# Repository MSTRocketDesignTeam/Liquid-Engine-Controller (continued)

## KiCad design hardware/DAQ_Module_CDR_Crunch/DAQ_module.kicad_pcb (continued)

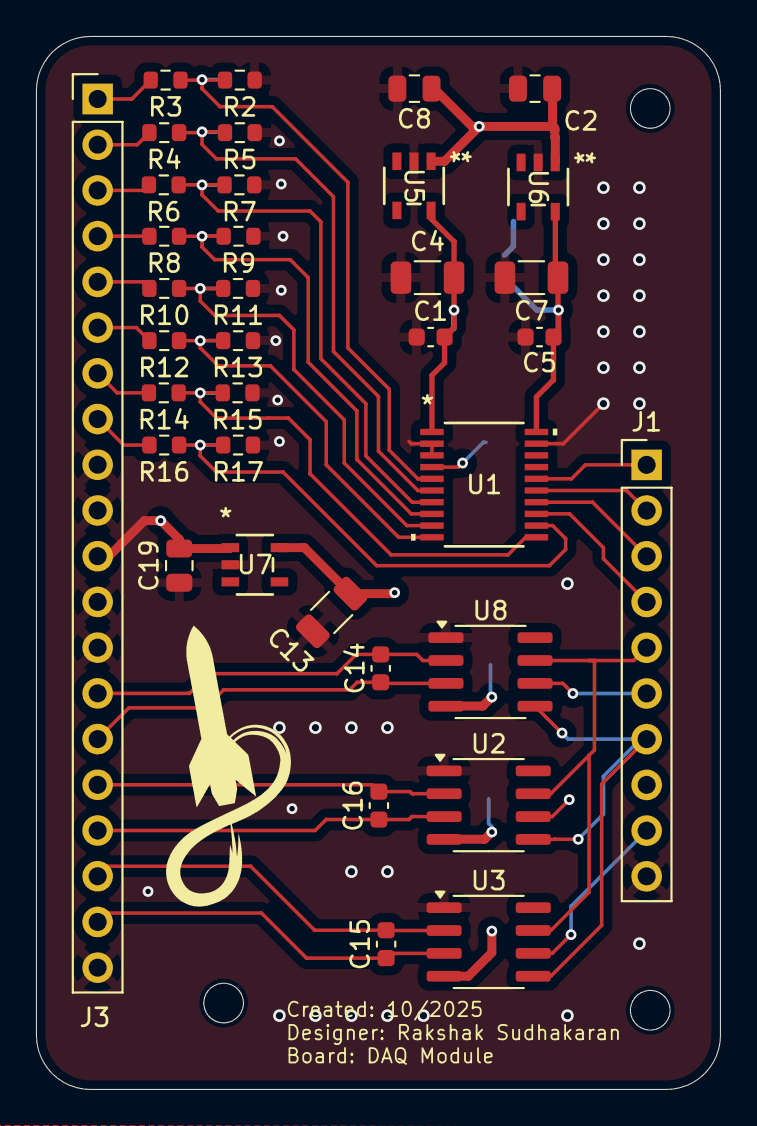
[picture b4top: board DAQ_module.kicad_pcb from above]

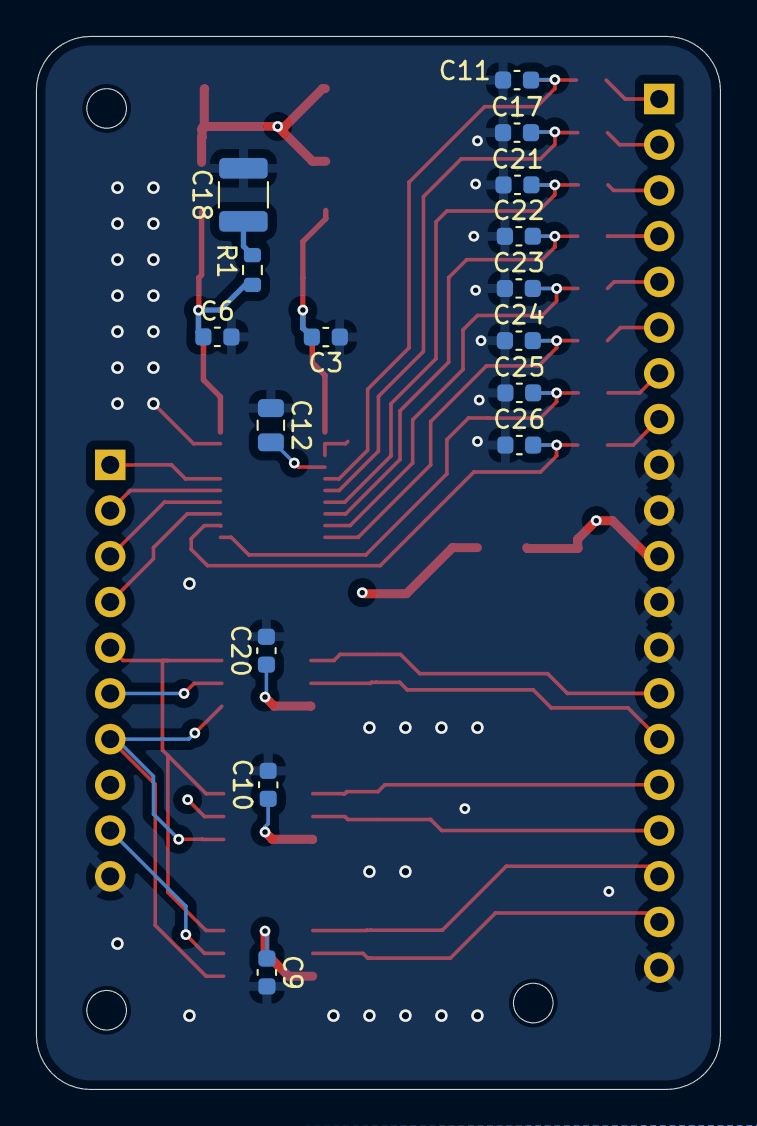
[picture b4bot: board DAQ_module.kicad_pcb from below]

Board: 4 copper layers, 38.0 x 58.5 mm, 52 parts (16 on the bottom side), 38 nets.

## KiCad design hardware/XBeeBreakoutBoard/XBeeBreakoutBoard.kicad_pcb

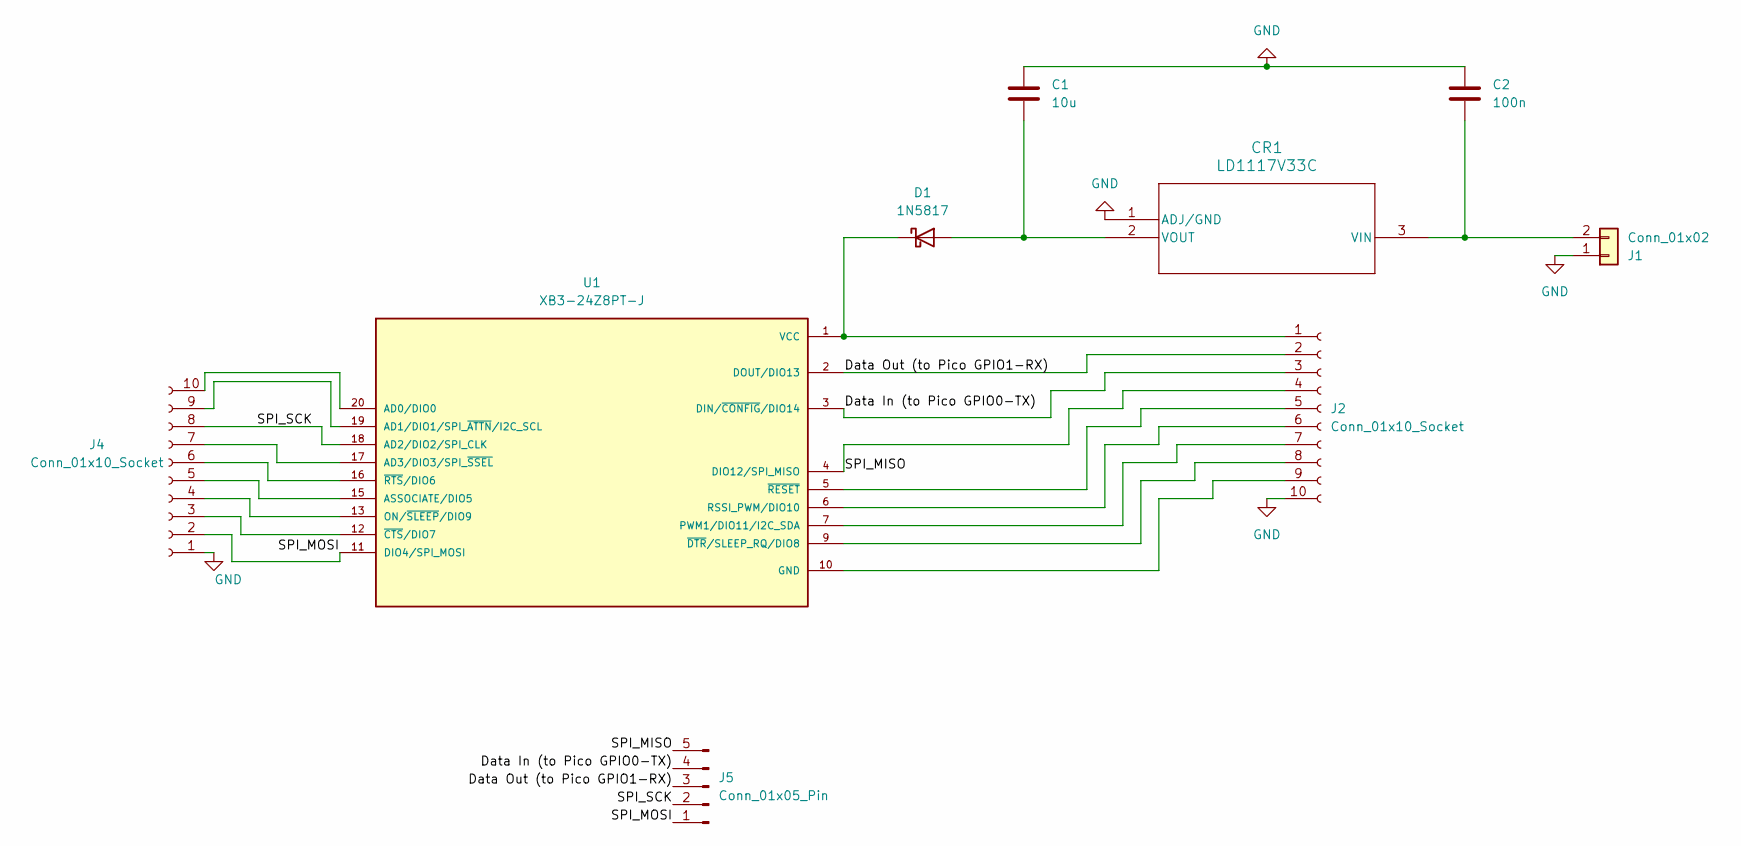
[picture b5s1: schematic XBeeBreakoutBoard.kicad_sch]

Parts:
C1: 10u; C_0805_2012Metric
C2: 100n; C_0603_1608Metric
CR1: LD1117V33C; TO-220_STM
D1: 1N5817; D_DO-41_SOD81_P10.16mm_Horizontal
J1: Conn_01x02; AMASS_XT30UPB-M_1x02_P5.0mm_Vertical
J2, J4: Conn_01x10_Socket; PinSocket_1x10_P2.54mm_Vertical
J5: Conn_01x05_Pin; PinSocket_1x05_P2.54mm_Vertical
U1: XB3-24Z8PT-J; XCVR_XB3-24Z8PT-J; PARTREV N/A

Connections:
/Data In (to Pico GPIO0-TX): J2.3, J5.4, U1.3 (DIN/~CONFIG/DIO14)
/Data Out (to Pico GPIO1-RX): J2.2, J5.3, U1.2 (DOUT/DIO13)
/SPI_MISO: J2.4, J5.5, U1.4 (DIO12/SPI_MISO)
/SPI_MOSI: J4.2, J5.1, U1.11 (DIO4/SPI_MOSI)
/SPI_SCK: J4.8, J5.2, U1.18 (AD2/DIO2/SPI_CLK)
GND: C1.1, C2.1, CR1.1 (ADJ/GND), J1.1, J2.10, J4.1
unnamed: C2.2, CR1.3 (VIN), J1.2
unnamed: C1.2, CR1.2 (VOUT), D1.2 (A)
unnamed: D1.1 (K), J2.1, U1.1 (VCC)
unnamed: J2.5, U1.5 (~RESET)
unnamed: J2.6, U1.6 (RSSI_PWM/DIO10)
unnamed: J2.7, U1.7 (PWM1/DIO11/I2C_SDA)
unnamed: J2.8, U1.9 (~DTR/SLEEP_RQ/DIO8)
unnamed: J2.9, U1.10 (GND)
unnamed: J4.3, U1.12 (~CTS/DIO7)
unnamed: J4.4, U1.13 (ON/~SLEEP/DIO9)
unnamed: J4.5, U1.15 (ASSOCIATE/DIO5)
unnamed: J4.6, U1.16 (~RTS/DIO6)
unnamed: J4.7, U1.17 (AD3/DIO3/SPI_~SSEL)
unnamed: J4.9, U1.19 (AD1/DIO1/SPI_~ATTN/I2C_SCL)
unnamed: J4.10, U1.20 (AD0/DIO0)

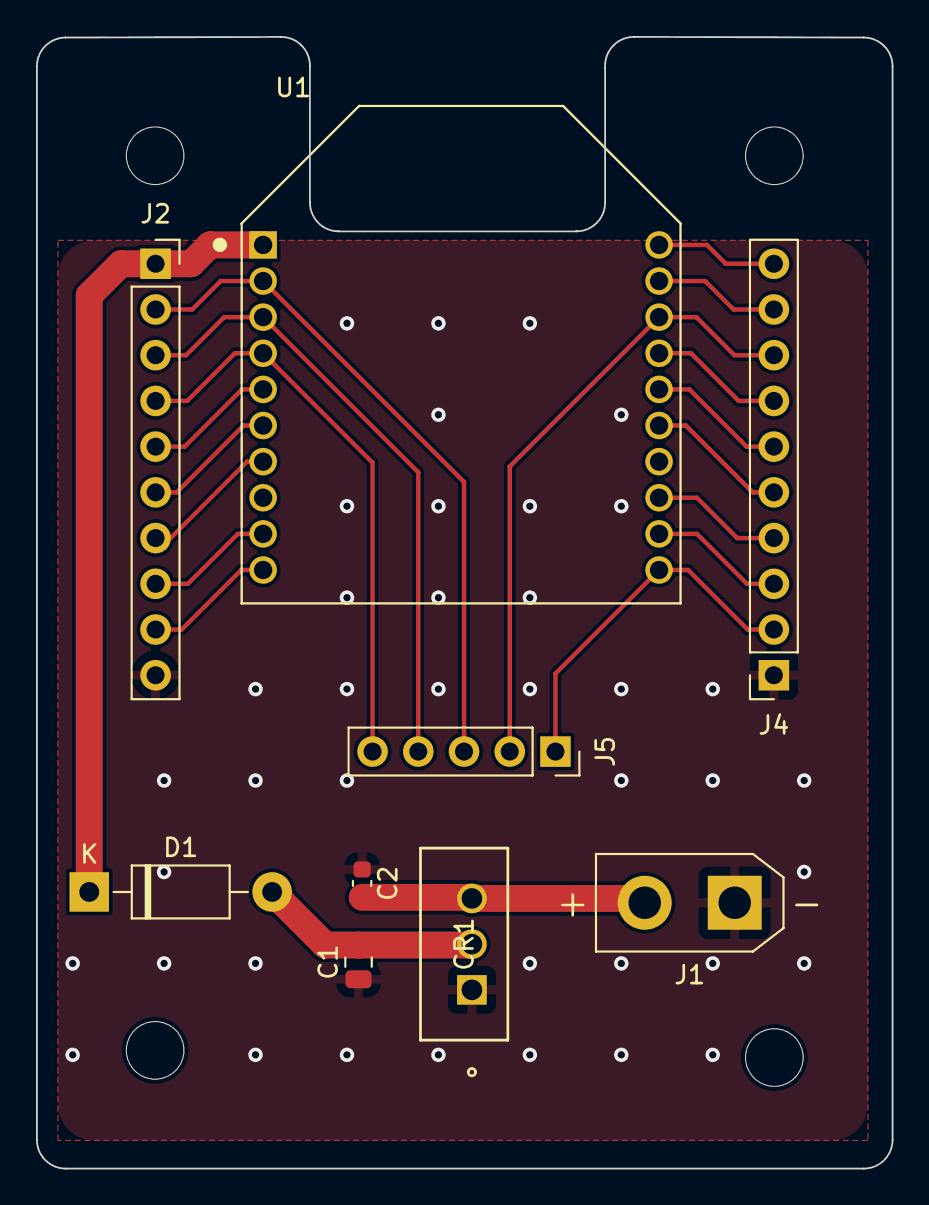
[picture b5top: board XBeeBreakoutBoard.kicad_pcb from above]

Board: 2 copper layers, 47.5 x 62.9 mm, 9 parts (0 on the bottom side), 21 nets.

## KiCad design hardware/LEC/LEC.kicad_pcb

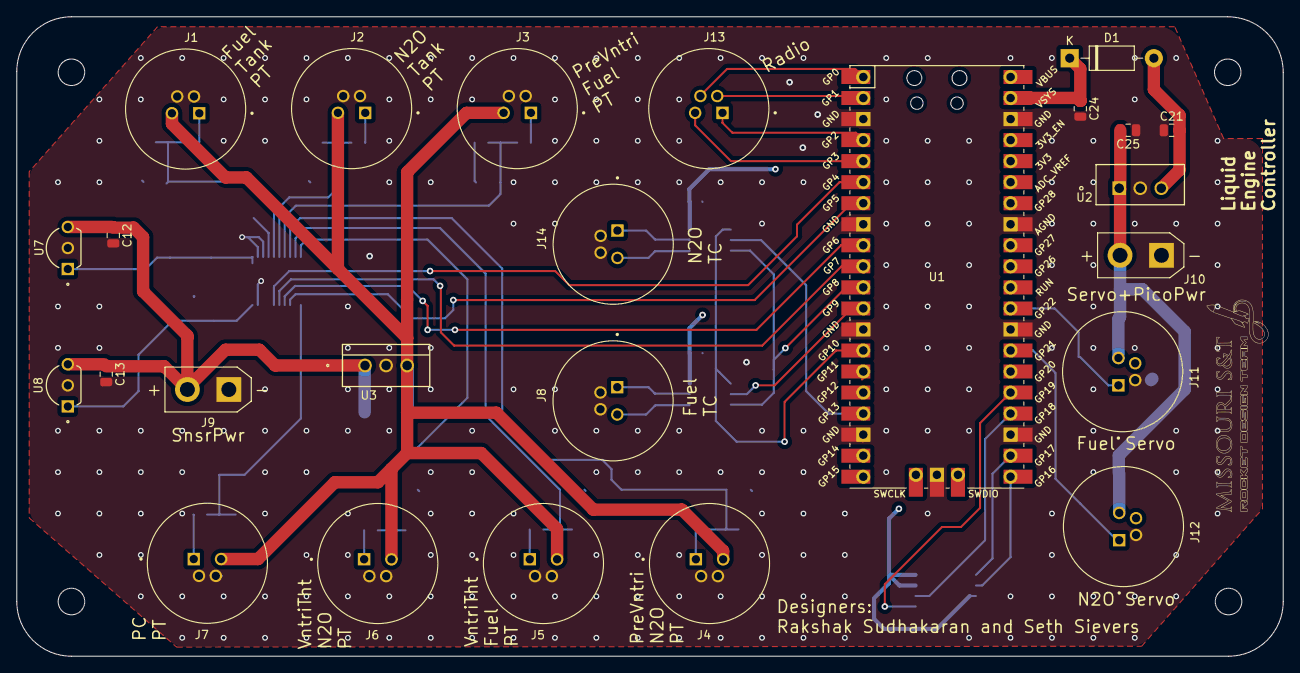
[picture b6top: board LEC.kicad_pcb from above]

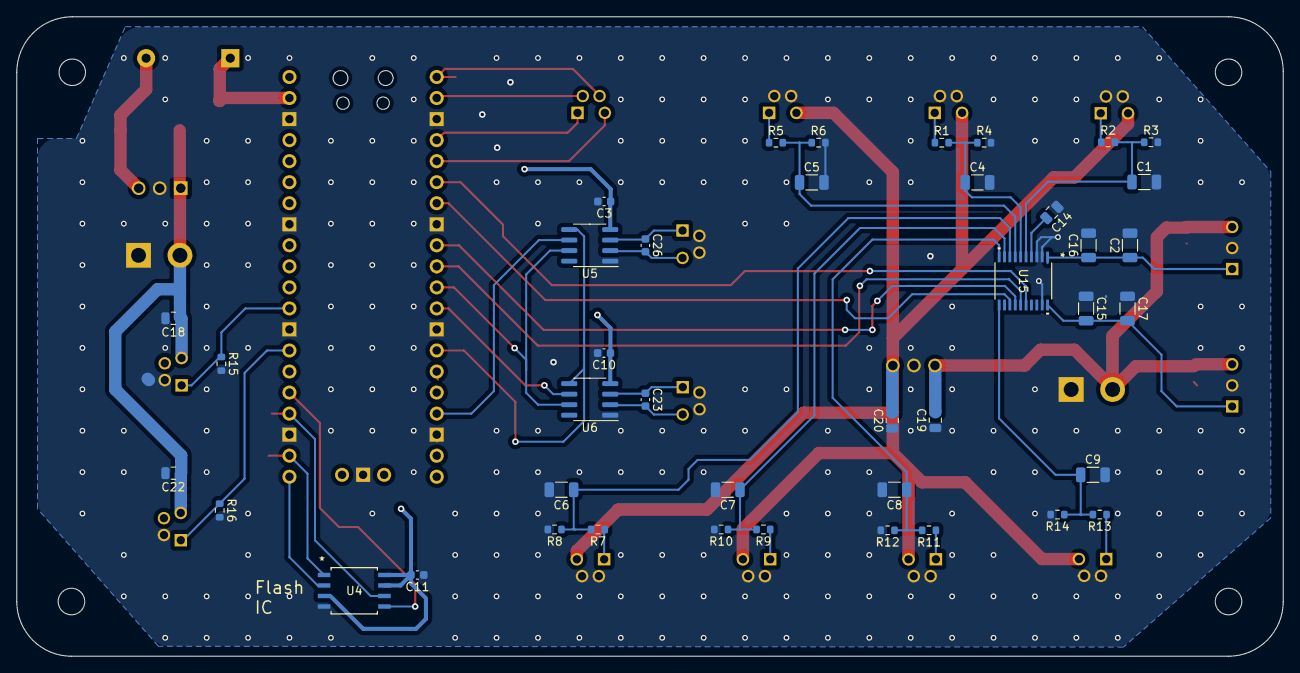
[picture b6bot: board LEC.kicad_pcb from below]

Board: 4 copper layers, 152.9 x 77.2 mm, 66 parts (41 on the bottom side), 46 nets.

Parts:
C1, C2, C4, C5, C6, C7, C8, C9, C15, C16, C17: 100n; C_1206_3216Metric
C3, C10, C11: 100n; C_0603_1608Metric
C12, C13, C14, C18, C19, C20, C21, C22, C24, C25: 10u; C_0805_2012Metric
C23, C26: 10n; C_0603_1608Metric
D1: 1N5817; D_DO-41_SOD81_P10.16mm_Horizontal
J1, J2, J3, J4, J5, J6, J7, J8, J11, J12, J13, J14: 54-00278; TENSILITY_54-00278
J9, J10: Conn_01x02; AMASS_XT30UPB-M_1x02_P5.0mm_Vertical
R1, R2, R3, R4, R5, R6, R7, R8, R9, R10, R11, R12, R13, R14, R15, R16: 10K; R_0603_1608Metric
U1: Pico; RPi_Pico_SMD_TH
U2: L7805; TO-220_STM
U3: MC7809CTG; TO-220AB_ONS
U4: W25Q128JVSIQ; SOIC_128JVSIQ_WIN
U5, U6: MAX31855KASA; SOIC-8_3.9x4.9mm_P1.27mm
U7, U8: L78L33ACZ; TO-92-TR_STM
U15: MCP3564RT-E/ST; TSSOP20_ST_MCH

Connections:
+3.3V: C3.1, C10.1, C11.2, U1.36 (3V3), U4.3 (WP_(IO2)), U4.7 (/HOLD_or_/RESET_(IO3)), U4.8 (VCC), U5.4 (V_CC), U6.4 (V_CC)
+12V: C18.1, C22.1, C25.2, J10.2, J11.3, J12.3, U2.1 (IN)
/ADC_Power_Circuit/AVDDOUT: C2.1, C16.1, U7.1 (VOUT), U15.1 (AVDD)
/ADC_Power_Circuit/DVDDOUT: C15.2, C17.2, U8.1 (VOUT), U15.20 (DVDD)
/ADC_Power_Circuit/VIN: C12.1, C13.1, C19.2, J9.2, U3.1 (INPUT), U7.3 (VIN), U8.3 (VIN)
/ExcIn: C20.2, J1.3, J2.3, J3.3, J4.3, J5.3, J6.3, J7.3, U3.3 (OUTPUT)
/GPIO0 (MISO): J13.4, U1.1 (GPIO0)
/GPIO1 (CS): J13.2, U1.2 (GPIO1)
/GPIO2 (SCK): J13.1, U1.4 (GPIO2)
/GPIO3 (MOSI): J13.3, U1.5 (GPIO3)
/GPIO4 (MISO): U1.6 (GPIO4), U15.16 (SDO)
/GPIO5 (CS): U1.7 (GPIO5), U15.13 (*CS)
/GPIO6 (SCK): U1.9 (GPIO6), U15.14 (SCK)
/GPIO7 (MOSI): U1.10 (GPIO7), U15.15 (SDI)
/GPIO8 (MISO): U1.11 (GPIO8), U5.7 (SO), U6.7 (SO)
/GPIO9 (CS): U1.12 (GPIO9), U6.6 (~CS)
/GPIO10 (SCK): U1.14 (GPIO10), U5.5 (SCK), U6.5 (SCK)
/GPIO13 (CS): U1.17 (GPIO13), U5.6 (~CS)
/GPIO16 (MISO): U1.21 (GPIO16), U4.2 (DO_(IO1))
/GPIO17 (CS): U1.22 (GPIO17), U4.1 (/CS)
/GPIO18 (SCK): U1.24 (GPIO18), U4.6 (CLK)
/GPIO19 (MOSI): U1.25 (GPIO19), U4.5 (DI_(IO0))
/Sig1: J1.1, R2.1
/Sig2: J2.1, R1.1
/Sig3: J3.1, R5.1
/Sig4: J4.1, R7.1
/Sig5: J5.1, R9.1
/Sig6: J6.1, R11.1
/Sig7: J7.1, R13.1
/lowPassFilter1/Sig_{out}: C4.1, R1.2, R4.1, U15.6 (CH1)
/lowPassFilter2/Sig_{out}: C5.1, R5.2, R6.1, U15.7 (CH2)
/lowPassFilter3/Sig_{out}: C6.1, R7.2, R8.1, U15.8 (CH3)
/lowPassFilter4/Sig_{out}: C7.1, R9.2, R10.1, U15.9 (CH4)
/lowPassFilter5/Sig_{out}: C8.1, R11.2, R12.1, U15.10 (CH5)
/lowPassFilter6/Sig_{out}: C9.1, R13.2, R14.1, U15.11 (CH6)
/lowPassFilter/Sig_{out}: C1.1, R2.2, R3.1, U15.5 (CH0)
GND: C1.2, C2.2, C3.2, C4.2, C5.2, C6.2, C7.2, C8.2, C9.2, C10.2, C11.1, C12.2, C13.2, C14.1, C15.1, C16.2, C17.1, C18.2, C19.1, C20.1, C21.1, C22.2, C24.2, C25.1, J1.2, J1.4, J2.2, J2.4, J3.2, J3.4, J4.2, J4.4, J5.2, J5.4, J6.2, J6.4, J7.2, J7.4, J8.2, J8.4, J9.1, J10.1, J11.2, J12.2, J14.2, J14.4, R3.2, R4.2, R6.2, R8.2, R10.2, R12.2, R14.2, R15.2, R16.2, U1.3 (GND), U1.8 (GND), U1.13 (GND), U1.18 (GND), U1.23 (GND), U1.28 (GND), U1.33 (AGND), U1.38 (GND), U1.42 (GND), U2.2 (GND), U3.2 (GROUND), U4.4 (GND), U5.1 (GND), U6.1 (GND), U7.2 (GND), U8.2 (GND), U15.2 (AGND), U15.3 (REFIN-), U15.19 (DGND)
unnamed: C21.2, D1.2 (A), U2.3 (OUT)
unnamed: C24.1, D1.1 (K), U1.39 (VSYS)
unnamed: J12.1, R16.1, U1.27 (GPIO21)
unnamed: J11.1, R15.1, U1.29 (GPIO22)
unnamed: C26.1, J14.1, U5.3 (T+)
unnamed: C26.2, J14.3, U5.2 (T-)
unnamed: C23.1, J8.1, U6.3 (T+)
unnamed: C23.2, J8.3, U6.2 (T-)
unnamed: C14.2, U15.4 (REFIN+/OUT)

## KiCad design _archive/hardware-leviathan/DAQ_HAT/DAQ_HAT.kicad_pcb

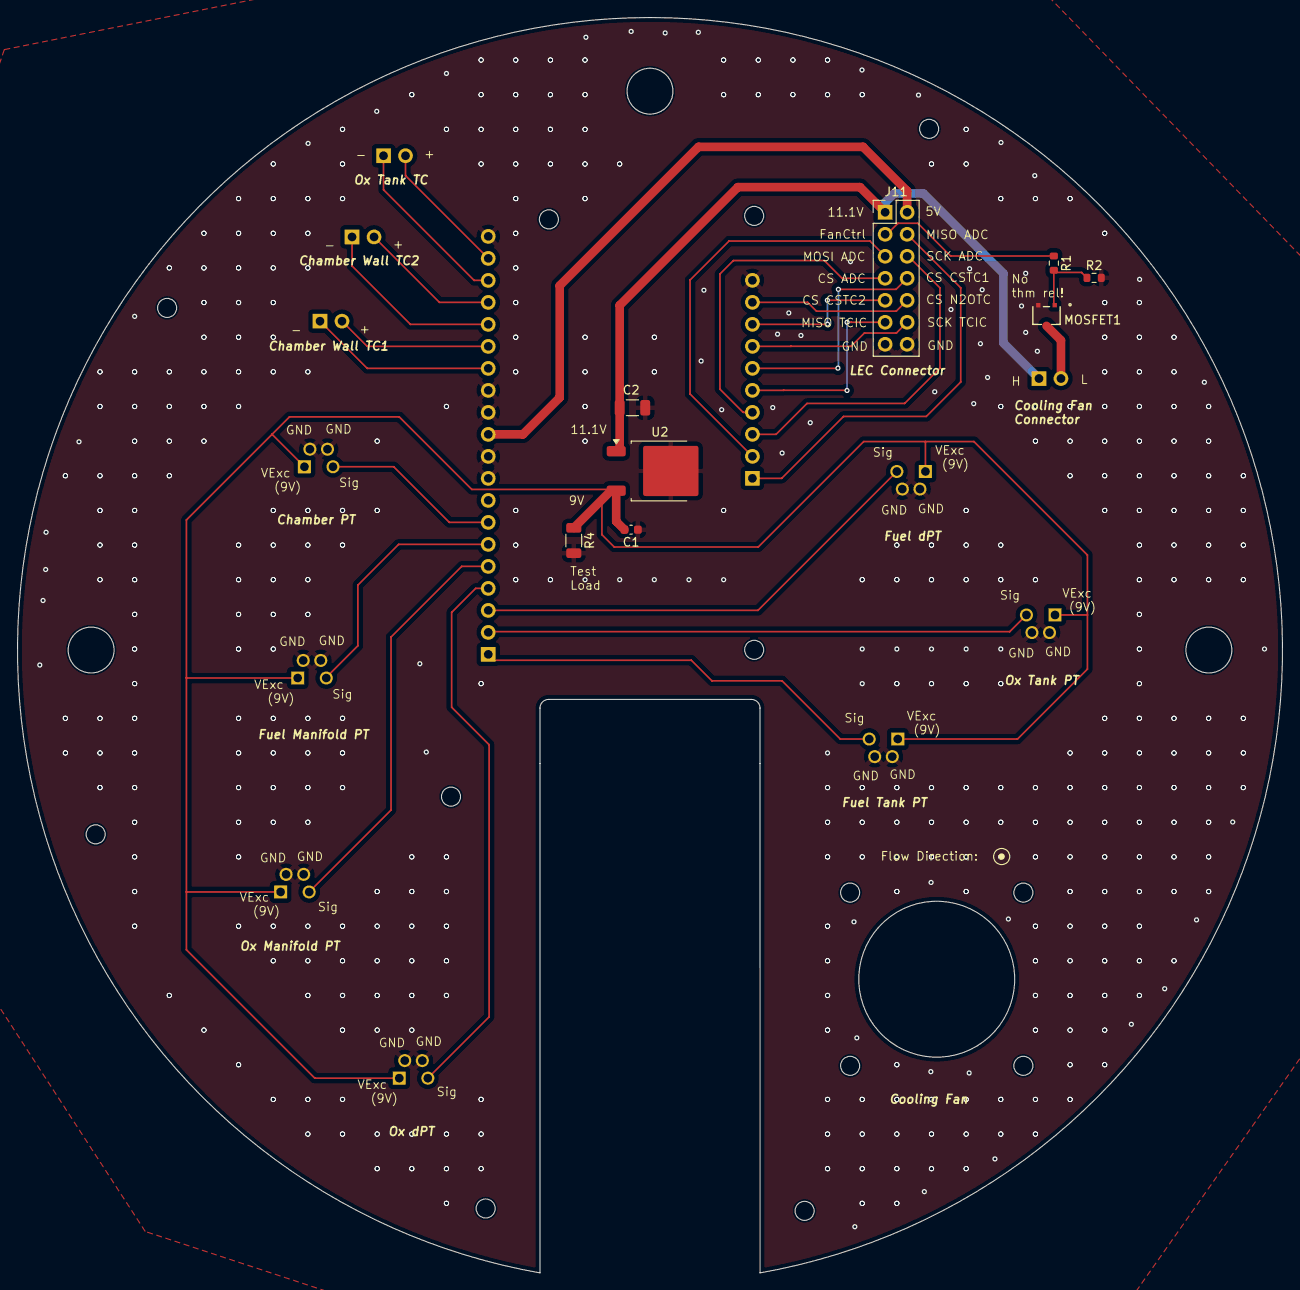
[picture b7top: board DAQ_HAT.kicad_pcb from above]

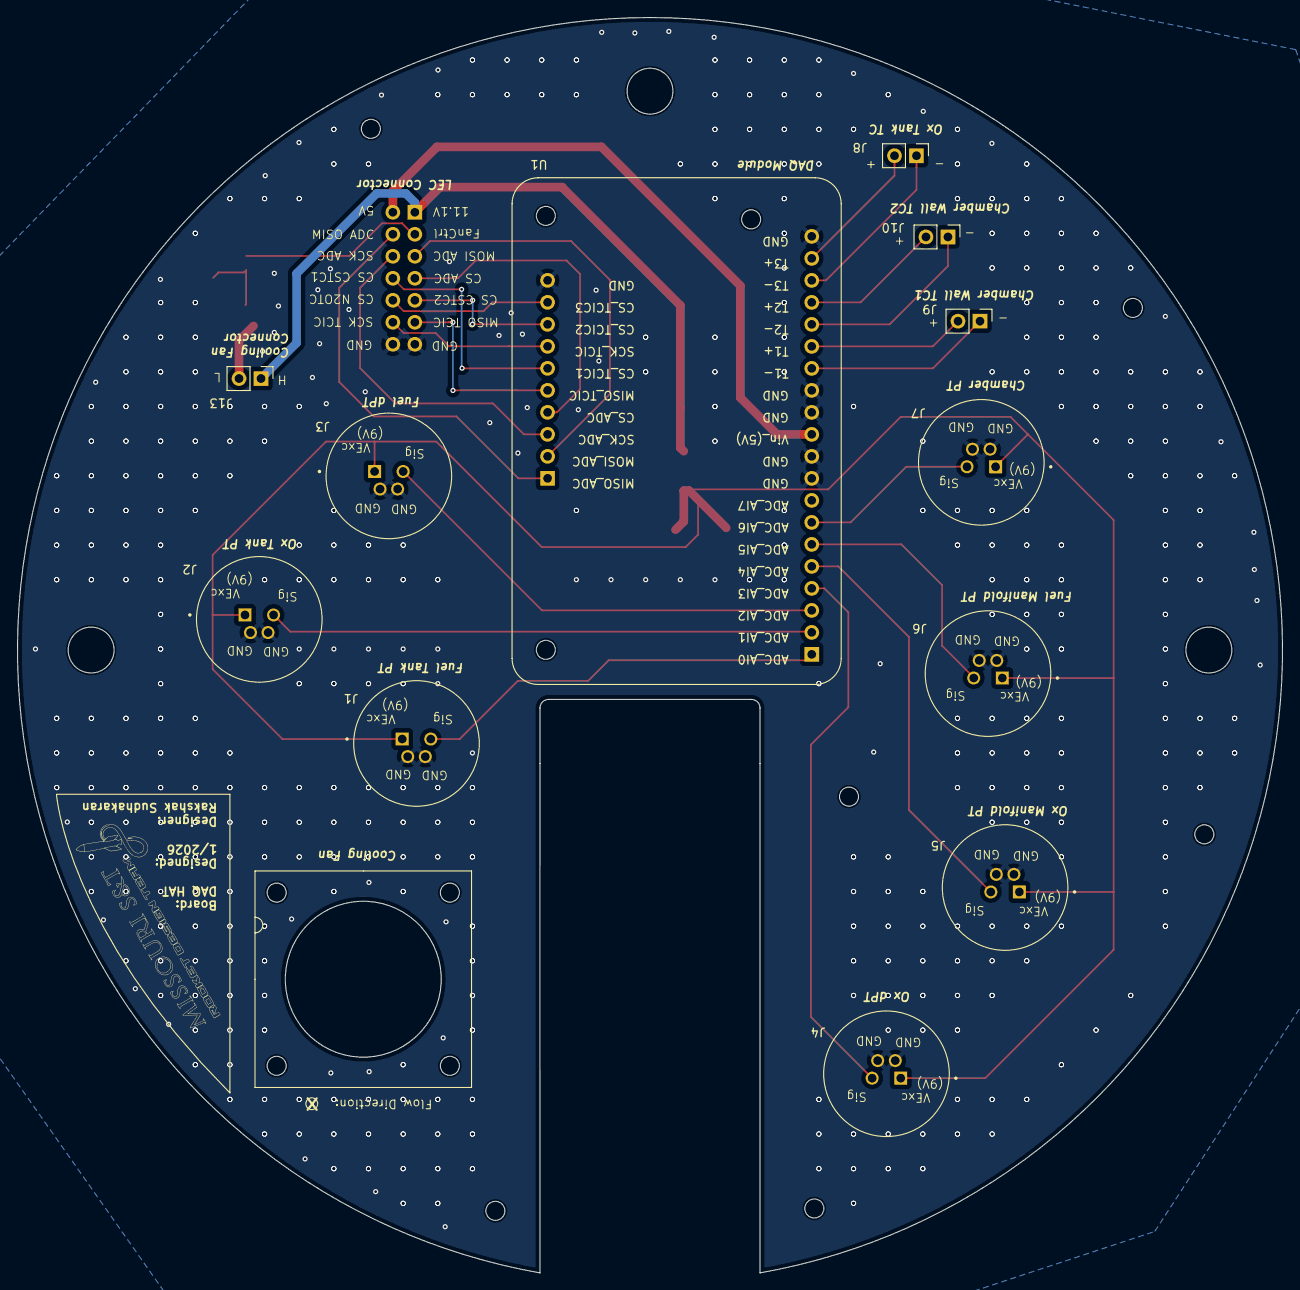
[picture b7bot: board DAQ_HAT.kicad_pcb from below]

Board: 2 copper layers, 146.0 x 144.9 mm, 20 parts (12 on the bottom side), 29 nets.

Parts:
C1: 100n; C_0603_1608Metric
C2: 0.33u; C_1206_3216Metric
J1: Fuel_Tank_PT; TENSILITY_54-00278
J2: Ox_Tank_PT; TENSILITY_54-00278
J3: Fuel_dPT; TENSILITY_54-00278
J4: Ox_dPT; TENSILITY_54-00278
J5: Ox_Manifold_PT; TENSILITY_54-00278
J6: Fuel_Manifold_PT; TENSILITY_54-00278
J7: Chamber_PT; TENSILITY_54-00278
J8: Ox_Tank_TC; PinHeader_1x02_P2.54mm_Vertical
J9: Chamber_Wall_TC1; PinHeader_1x02_P2.54mm_Vertical
J10: Chamber_Wall_TC2; PinHeader_1x02_P2.54mm_Vertical
J11: Conn_02x07_Odd_Even; PinHeader_2x07_P2.54mm_Vertical
J13: Fan_Conn; PinHeader_1x02_P2.54mm_Vertical
MOSFET1: SSM3K2615R_LF; SOT-23F_TOS
R1: 100; R_0603_1608Metric
R2: 10K; R_0603_1608Metric
R4: 1k; R_1206_3216Metric
U1: DAQ_Module
U2: UA78M09CKVURG3; TO-252-2

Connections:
11.1V: C2.2, J11.1, J13.1, U2.1 (Vcc)
+5V: J11.2, U1.11 (Vin_(5V))
+9V: C1.2, J1.1, J2.1, J3.1, J4.1, J5.1, J6.1, J7.1, R4.1, U2.3 (OUT)
/ADC_AI0_(Fuel_Tank_PT): J1.3, U1.1 (ADC_AI0)
/ADC_AI1_(Ox_Tank_PT): J2.3, U1.2 (ADC_AI1)
/ADC_AI2_(Fuel_dPT): J3.3, U1.3 (ADC_AI2)
/ADC_AI3_(Ox_dPT): J4.3, U1.4 (ADC_AI3)
/ADC_AI4_(Ox_Manifold_PT): J5.3, U1.5 (ADC_AI4)
/ADC_AI5_(Fuel_Manifold_PT): J6.3, U1.6 (ADC_AI5)
/ADC_AI6_(Chamber_PT): J7.3, U1.7 (ADC_AI6)
/GPIO4 (MISO_ADC): J11.4, U1.21 (MISO_ADC)
/GPIO5 (CS_ADC): J11.7, U1.24 (CS_ADC)
/GPIO6 (SCK_ADC): J11.6, U1.23 (SCK_ADC)
/GPIO7 (MOSI_ADC): J11.5, U1.22 (MOSI_ADC)
/GPIO8 (MISO_TCIC): J11.11, U1.25 (MISO_TCIC)
/GPIO9 (CS Chamber Shell_1): J11.8, U1.26 (CS_TCIC1)
/GPIO10 (SCK_TCIC): J11.12, U1.27 (SCK_TCIC)
/GPIO12 (CS N2O): J11.10, U1.29 (CS_TCIC3)
/GPIO13 (CS Chamber Shell_2): J11.9, U1.28 (CS_TCIC2)
/GPIO14 (FanCtrl): J11.3, R1.1
/T+ (Chamber Shell_1): J9.2, U1.15 (T1+)
/T+ (Chamber Shell_2): J10.2, U1.17 (T2+)
/T+ (N2O): J8.2, U1.19 (T3+)
/T- (Chamber Shell_1): J9.1, U1.14 (T1-)
/T- (Chamber Shell_2): J10.1, U1.16 (T2-)
/T- (N2O): J8.1, U1.18 (T3-)
GND: C1.1, C2.1, J1.2, J1.4, J2.2, J2.4, J3.2, J3.4, J4.2, J4.4, J5.2, J5.4, J6.2, J6.4, J7.2, J7.4, J11.13, J11.14, MOSFET1.2, R2.2, R4.2, U1.9 (GND), U1.10 (GND), U1.12 (GND), U1.13 (GND), U1.20 (GND), U1.30 (GND), U2.2 (GND)
unnamed: J13.2, MOSFET1.3
unnamed: MOSFET1.1, R1.2, R2.1

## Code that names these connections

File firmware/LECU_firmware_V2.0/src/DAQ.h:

#ifndef DAQ_H
#define DAQ_H

#include <Arduino.h>
#include <SPI.h>
#include "MCP3x6x_Type_Definitions.h"                     // Variable definitions header-file.
#include "MCP3x6x_ADC_Definitions.h"                      // ADC definitions header-file.
#include "MCP3x6x_Peripheral_Definitions.h"               // Peripheral definitions header-file.
#include "MCP3x6x_SPI_Definitions.h"                      // SPI definitions header-file.


// -------------------------
// Pin Assignments
// -------------------------
extern int MCP3564_CS_PIN;
extern int TC1_CS_PIN;
extern int TC2_CS_PIN;
extern int TC3_CS_PIN;

// -------------------------
// Initialization
// -------------------------
void init_DAQ();

// -------------------------
// High‑level DAQ read function
// -------------------------
void read_DAQ_module(
    volatile uint32_t &AI0Reading,
    volatile uint32_t &AI1Reading,
    volatile uint32_t &AI2Reading,
    volatile uint32_t &AI3Reading,
    volatile uint32_t &AI4Reading,
    volatile uint32_t &AI5Reading,
    volatile uint32_t &AI6Reading,
    volatile uint32_t &TC1Reading,
    volatile uint32_t &TC2Reading,
    volatile uint32_t &TC3Reading
);

#endif

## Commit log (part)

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2024-09-08 Update README.md
    Modeled updates off of commit 7d665da of README.md of SRAD-Flight-Computer repo.
2024-09-08 Update README.md
    Updated LFC to LEC as per design decision
2024-09-10 Updated repo structure
2024-10-19 Initial commit of LEC KiCad files
2024-11-09 Added LPFs and updated power circuits. Tidied up a bit
2024-11-13 Updated LVR selection and other optimizations. Need to update footprints and symbols
2024-11-13 Removed resistors on ADC power lines
2024-11-16 Updated wiring of flash chip, connected 3V3 net, and added PWM pulldowns
2024-11-17 Added bulk capacitors to ADC LVRs, servos, and pico power inputs
2024-11-22 Schematic done
2024-11-23 Added decoupling capacitor across thermocouple inputs
2024-11-29 Initial commit of PCB files, updated schematic syntax to smooth PCB design workflow. Need to fill ground planes and other necessary updates
2024-12-03 Added mounting holes, ground planes, and via stiching
2024-12-03 Added labeling, moved ADC decoupling caps closer to ADC
2024-12-09 Updated pin mapping of radio connector for cleaner routing
2024-12-12 Final updates
2024-12-12 Added production files
2024-12-12 Updated schematic documentation, more production files
2025-01-20 added adc example
2025-01-20 misc sync
2025-02-08 Initial commit of XBee Breakout Board
2025-02-12 XBee Breakout production files
2025-06-21 Baseline commit, all files in this commit were used to successfully launch Phoenix
2025-06-21 First commit of 25-26 design cycle. Structure update
2025-06-21 Adding readme files
2025-10-03 Added XBEE module schematic and pcb
2025-10-04 DAQ Module
2025-10-08 Added full KiCad project for RF module
2025-10-10 Push of most recent schematic and PCB
2025-10-13 Started a gitignore. Long overdue );
2025-10-13 LECMainBoard initial commit. Ready for schematic review
2025-10-13 Reverted to previous commit to undo any accidental changes
2025-10-13 Added name to schematic
2025-10-16 Temp commit to upload changes to buck converter circuit
2025-10-19 Implemented fixes. Ready for 2nd review
2025-10-19 Routed XBEE PCB
2025-10-25 Intermediate commit, need to fix servo connector footprints
2025-10-25 Fixed all footprints. Defined PCB edge, arbitrarily placed components
2025-10-27 Initial commit of DAQ_module revision to meet deadlines
2025-10-27 Added GPIO clamping diodes, sufficient buck output capacitance, UVLO divider, and 3V3_EN diode
2025-10-29 Ready for final review. Added downloadable footprint and symbol of board
2025-10-29 Fixed logo and mounting holes
2025-10-29 Improved some via spacing
2025-10-30 Added fix for downloadable footprint of DAQ Module CDR Crunch for 3rd mounting hole
2025-10-30 Fixed footprint and symbol input conn pinout to reflect schematic and PCB
2025-10-31 Final revision of XBEE board
2025-11-07 Added part numbers and datasheets
2025-11-08 Fixed some traces' layer selection
2025-11-15 Experimenting with alternate layout bc no SMA connector
2025-11-15 Updated silkscreen text
2025-11-15 Routed revised XBEE PCB layout
2025-11-20 Done
2026-01-25 Finished PCBs
2026-03-07 Basic servo test firmware for LEC flow-test
2026-03-18 Updated radio parse for new message format
2026-04-08 Refactored for platformIO
2026-05-13 Baseline pre-LEC-DAQ functionality
2026-05-13 DAQ works fine, the GSEC Pico doesn't seem to be processing it correctly. No latency in comms
2026-05-14 Working LEC and GSE DAQ commit! No latency
2026-05-19 Added Flash IC functionality and cooling fan usage
